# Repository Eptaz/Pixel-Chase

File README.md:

Polytech project leaded by @Rapha-tech and @Eptaz

Creating an Arcade Game named Pixel Chase.

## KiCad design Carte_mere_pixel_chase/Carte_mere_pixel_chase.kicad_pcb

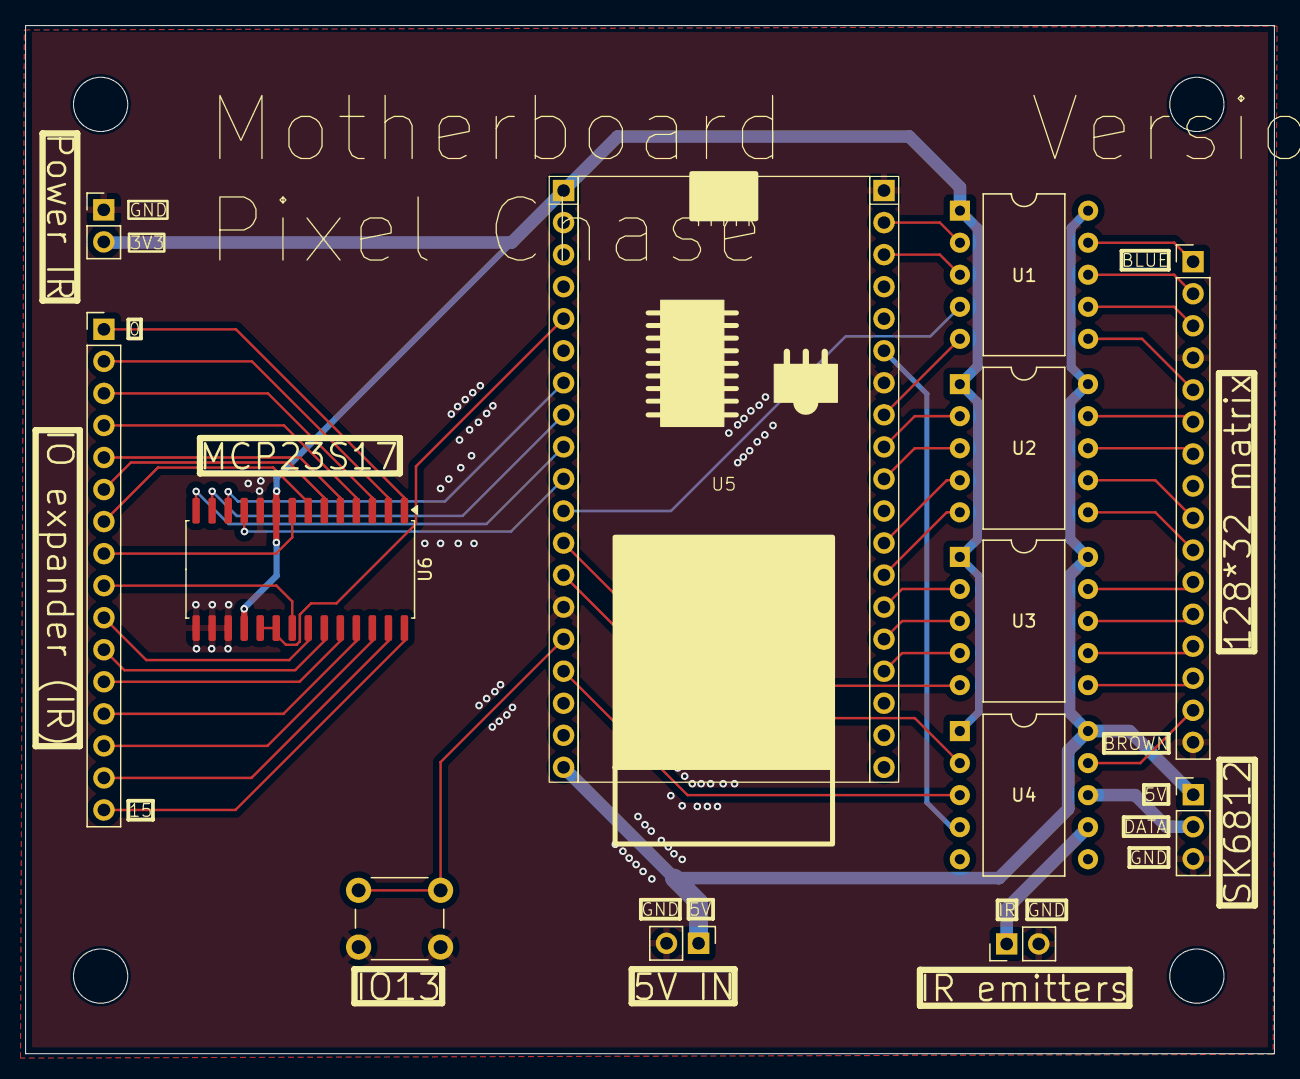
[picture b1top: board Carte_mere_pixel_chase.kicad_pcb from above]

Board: 2 copper layers, 99.0 x 81.5 mm, 17 parts (0 on the bottom side), 55 nets.

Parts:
H1, H2, H3, H4: MountingHole; MountingHole_4.3mm_M4
J1: Conn_01x02_5V_IN; PinHeader_1x02_P2.54mm_Vertical
J2: Conn_01x16_Matrix; PinHeader_1x16_P2.54mm_Vertical
J3: Conn_01x03_SK6812; PinHeader_1x03_P2.54mm_Vertical
J4: Conn_01x16_IR_receivers; PinHeader_1x16_P2.54mm_Vertical
J5: Conn_01x02_3V3+GND IR_receivers; PinHeader_1x02_P2.54mm_Vertical
J6: Conn_01x02_IR_emitters; PinHeader_1x02_P2.54mm_Vertical
SW1: SW_Push; SW_PUSH_6mm
U1, U2, U3, U4: DIP-10_W10.16mm
U5: ESP32-S3 dev module; esp32 dev module
U6: MCP23S17_SO; SOIC-28W_7.5x17.9mm_P1.27mm

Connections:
+3V3: J5.1, U1.1 (LV), U2.1 (LV), U3.1 (LV), U4.1 (LV), U5.1 (3V3), U6.9 (VDD), U6.18 (~RESET)
+5V: J1.1, J3.1, U1.10 (HV), U2.10 (HV), U3.10 (HV), U4.10 (HV), U5.19 (5V)
B0: U1.4 (L3), U5.11 (D27)
GND: J1.2, J2.4, J2.16, J3.3, J5.2, J6.2, SW1.1, U5.14 (GND), U5.20 (GND), U5.26 (GND), U6.10 (VSS), U6.15 (A0), U6.16 (A1), U6.17 (A2)
INTERRUPT: U5.5 (D34), U6.19 (INTB), U6.20 (INTA)
IR_LED: U4.4 (L3), U5.25 (D21)
LATCH: U3.5 (L4), U5.12 (D14)
unnamed: J2.1, U1.9 (H1)
unnamed: J2.2, U1.8 (H2)
unnamed: J2.3, U1.7 (H3)
unnamed: J2.5, U1.6 (H4)
unnamed: J2.6, U2.9 (H1)
unnamed: J2.7, U2.8 (H2)
unnamed: J2.9, U2.7 (H3)
unnamed: J2.10, U2.6 (H4)
unnamed: J2.11, U3.9 (H1)
unnamed: J2.12, U3.8 (H2)
unnamed: J2.13, U3.7 (H3)
unnamed: J2.14, U3.6 (H4)
unnamed: J2.15, U4.9 (H1)
unnamed: J3.2, U4.8 (H2)
unnamed: J4.1, U6.1 (GPB0)
unnamed: J4.2, U6.2 (GPB1)
unnamed: J4.3, U6.3 (GPB2)
unnamed: J4.4, U6.4 (GPB3)
unnamed: J4.5, U6.5 (GPB4)
unnamed: J4.6, U6.6 (GPB5)
unnamed: J4.7, U6.7 (GPB6)
unnamed: J4.8, U6.8 (GPB7)
unnamed: J4.9, U6.21 (GPA0)
unnamed: J4.10, U6.22 (GPA1)
unnamed: J4.11, U6.23 (GPA2)
unnamed: J4.12, U6.24 (GPA3)
unnamed: J4.13, U6.25 (GPA4)
unnamed: J4.14, U6.26 (GPA5)
unnamed: J4.15, U6.27 (GPA6)
unnamed: J4.16, U6.28 (GPA7)
unnamed: J6.1, U4.7 (H3)
unnamed: U1.2 (L1), U5.21 (D23)
unnamed: U1.3 (L2), U5.22 (D22)
unnamed: U1.5 (L4), U5.27 (D19)
unnamed: U2.2 (L1), U5.28 (D18)
unnamed: U2.3 (L2), U5.29 (D5)
unnamed: U2.4 (L3), U5.31 (D16)
unnamed: U2.5 (L4), U5.32 (D4)
unnamed: U3.2 (L1), U5.33 (D0)
unnamed: U3.3 (L2), U5.34 (D2)
unnamed: U3.4 (L3), U5.35 (D15)
unnamed: SW1.2, U5.15 (D13)
OE: U4.2 (L1), U5.13 (D12)
SK6812: U4.3 (L2), U5.16 (D2)
SPI_CS: U5.10 (D26), U6.11 (~CS)
SPI_MISO: U5.8 (D33), U6.13 (SI)
SPI_MOSI: U5.9 (D25), U6.14 (SO)
SPI_SCK: U5.7 (D32), U6.12 (SCK)

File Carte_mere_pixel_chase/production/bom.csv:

Designator,Footprint,Quantity,Value,LCSC Part #
J1,PinHeader_1x02_P2.54mm_Vertical,1,Conn_01x02_5V_IN,
J2,PinHeader_1x16_P2.54mm_Vertical,1,Conn_01x16_Matrix,
J3,PinHeader_1x03_P2.54mm_Vertical,1,Conn_01x03_SK6812,
J4,PinHeader_1x16_P2.54mm_Vertical,1,Conn_01x16_IR_receivers,
J5,PinHeader_1x02_P2.54mm_Vertical,1,Conn_01x02_3V3+GND IR_receivers,
J6,PinHeader_1x02_P2.54mm_Vertical,1,Conn_01x02_IR_emitters,
SW1,SW_PUSH_6mm,1,SW_Push,
"U1, U2, U3, U4",DIP-10_W10.16mm,4,~,
U5,esp32 dev module,1,ESP32-S3 dev module,
U6,SOIC-28W_7.5x17.9mm_P1.27mm,1,MCP23S17_SO,

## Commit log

2025-05-08 Create test
2025-05-08 Delete
2025-05-08 README.md
